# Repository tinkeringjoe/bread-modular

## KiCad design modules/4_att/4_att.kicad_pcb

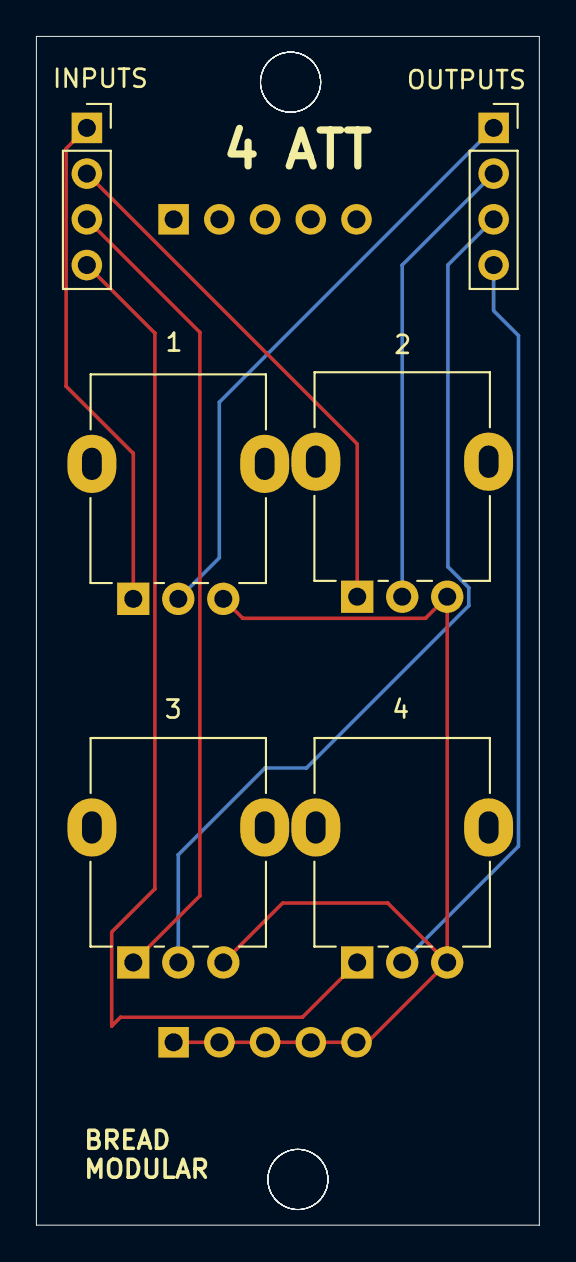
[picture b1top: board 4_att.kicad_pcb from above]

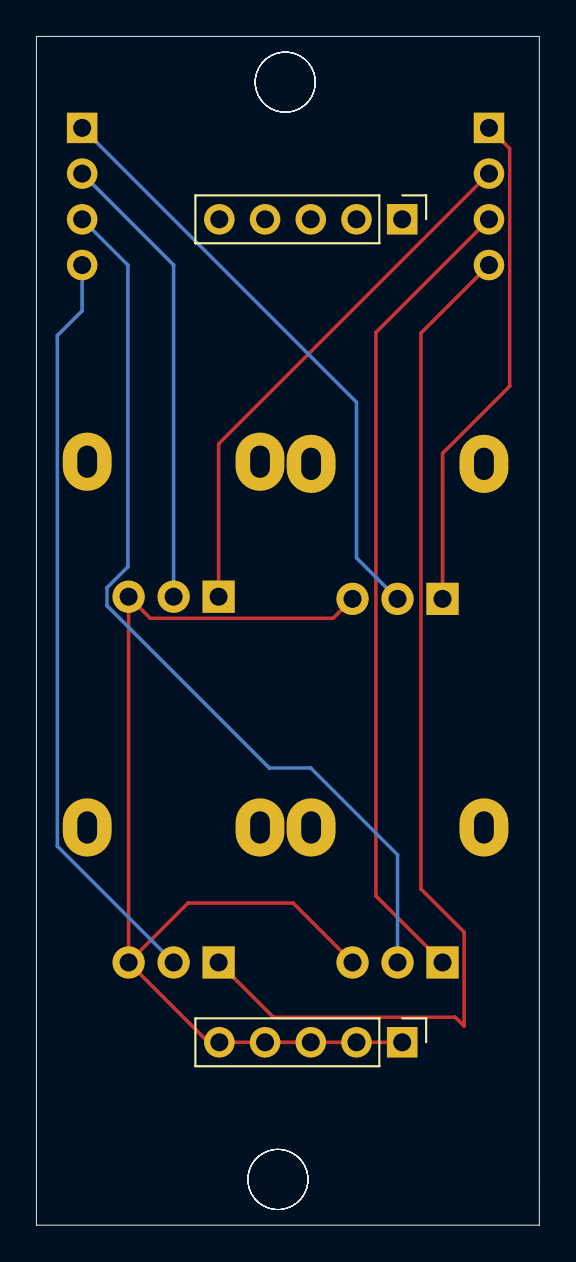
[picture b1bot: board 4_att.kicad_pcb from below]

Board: 2 copper layers, 27.9 x 66.0 mm, 8 parts (2 on the bottom side), 9 nets.

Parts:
1, 2, 3, 4: 100K; Potentiometer_Alpha_RD901F-40-00D_Single_Vertical
5V1: Conn_01x05_Pin; PinHeader_1x05_P2.54mm_Vertical
GND1: Conn_01x05_Pin; PinHeader_1x05_P2.54mm_Vertical
INPUTS: Conn_01x04_Socket; PinSocket_1x04_P2.54mm_Vertical
OUTPUTS: Conn_01x04_Socket; PinSocket_1x04_P2.54mm_Vertical

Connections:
GND: 1.3, 2.3, 3.3, 4.3, GND1.1, GND1.2, GND1.3, GND1.4, GND1.5
IN 1: 1.1, INPUTS.1
IN 2: 2.1, INPUTS.2
IN 3: 3.1, INPUTS.3
IN 4: 4.1, INPUTS.4
OUT 1: 1.2, OUTPUTS.1
OUT 2: 2.2, OUTPUTS.2
OUT 3: 3.2, OUTPUTS.3
OUT 4: 4.2, OUTPUTS.4

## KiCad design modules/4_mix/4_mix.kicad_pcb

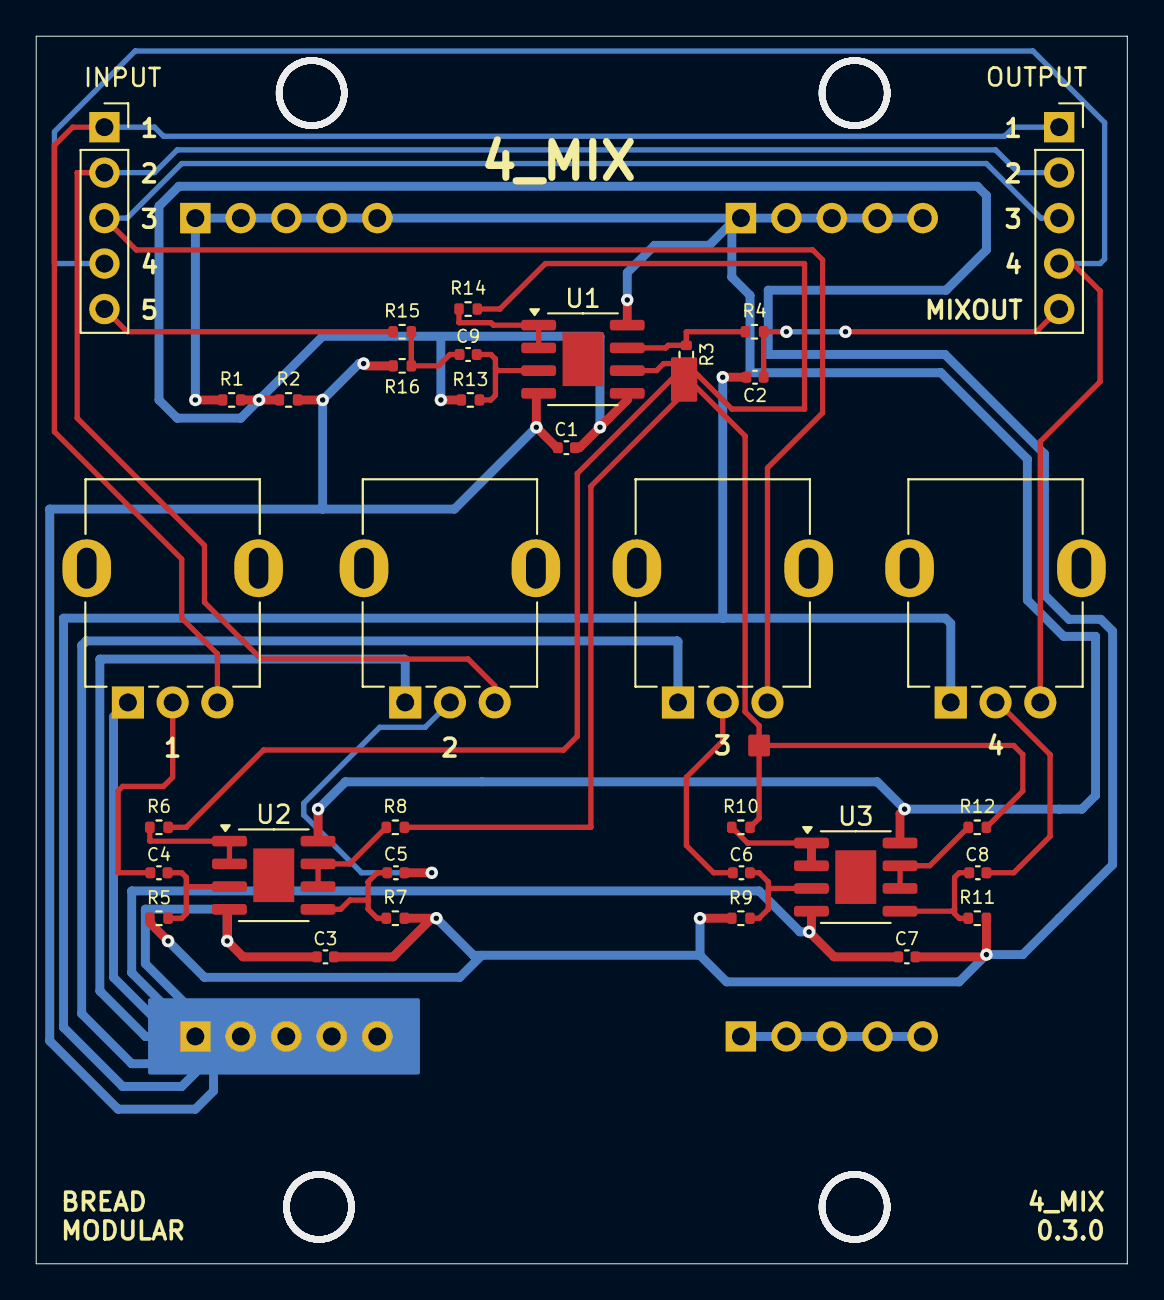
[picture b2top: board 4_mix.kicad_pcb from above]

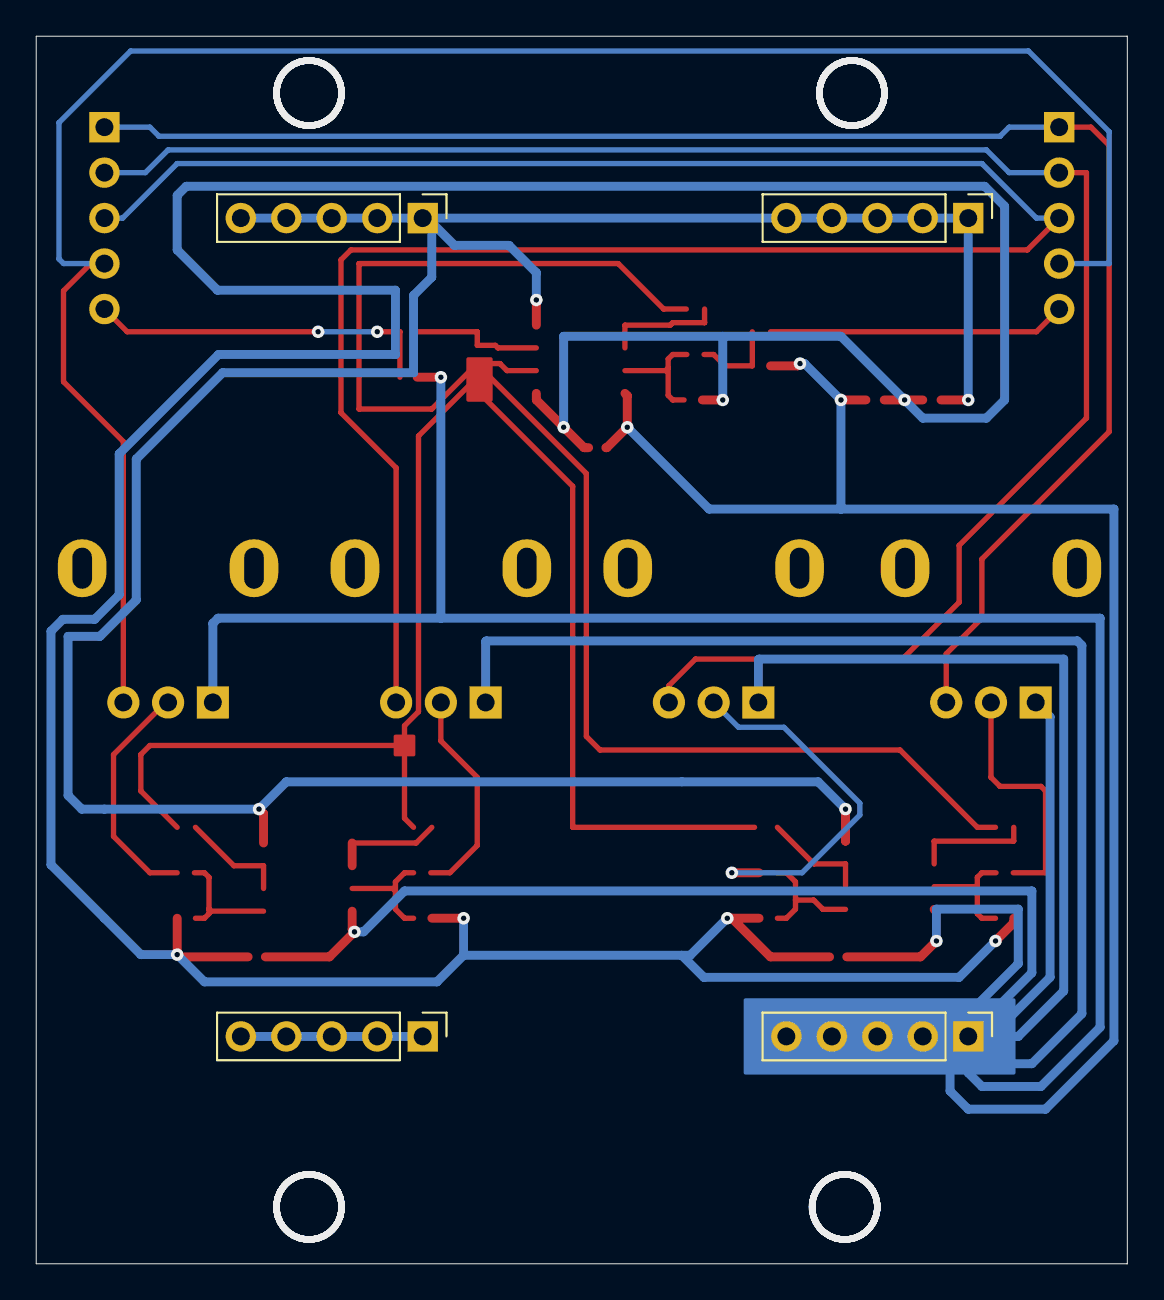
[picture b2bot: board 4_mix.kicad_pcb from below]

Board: 2 copper layers, 61.0 x 68.6 mm, 38 parts (4 on the bottom side), 27 nets.

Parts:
1, 2, 3, 4: 50k; Potentiometer_RV09
5V1, 5V2: Conn_01x05_Pin; PinHeader_1x05_P2.54mm_Vertical
C1, C3, C4, C5, C6, C7, C8, C9: 0.1uf; C_0402_1005Metric
C2: 0.01uf; C_0402_1005Metric
GND1, GND2: Conn_01x05_Pin; PinHeader_1x05_P2.54mm_Vertical
INPUT: Conn_01x05_Socket; PinSocket_1x05_P2.54mm_Vertical
OUTPUT: Conn_01x05_Socket; PinSocket_1x05_P2.54mm_Vertical
R1, R2, R4, R15: 1k; R_0402_1005Metric
R3, R5, R6, R7, R8, R9, R10, R11, R12, R13, R14: 100k; R_0402_1005Metric
R16: 51k; R_0402_1005Metric
U1, U2, U3: TL072; SOIC-8-1EP_3.9x4.9mm_P1.27mm_EP2.29x3mm

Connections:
2.5V: C1.2, C3.2, C7.2, R1.2, R2.1, R5.2, R7.2, R9.2, R11.2, R13.2, U1.5 (+)
+5V: 5V1.1, 5V1.2, 5V1.3, 5V1.4, 5V1.5, 5V2.1, 5V2.2, 5V2.3, 5V2.4, 5V2.5, R1.1, U1.8 (V+), U2.8 (V+), U3.8 (V+)
GND: 1.1, 2.1, 3.1, 4.1, C1.1, C2.2, C3.1, C7.1, GND1.1, GND1.2, GND1.3, GND1.4, GND1.5, R2.2, R16.2, U1.4 (V-), U2.4 (V-), U3.4 (V-)
IN_1: 1.3, INPUT.1, OUTPUT.1
IN_2: 2.3, INPUT.2, OUTPUT.2
IN_3: 3.3, INPUT.3, OUTPUT.3
IN_4: 4.3, INPUT.4, OUTPUT.4
IN_5: INPUT.5, R15.1
MIXOUT: C2.1, OUTPUT.5, R4.2
unnamed: 1.2, C4.1
unnamed: 2.2, C5.1
unnamed: 3.2, C6.1
unnamed: 4.2, C8.1
unnamed: C9.1, R15.2, R16.1
unnamed: GND2.1, GND2.2, GND2.3, GND2.4, GND2.5
unnamed: R3.2, R4.1, U1.7
unnamed: C9.2, R13.1, U1.3 (+)
unnamed: R3.1, R6.2, R8.2, R10.2, R12.2, R14.2, U1.6 (-)
unnamed: C4.2, R5.1, U2.3 (+)
unnamed: R6.1, U2.1, U2.2 (-)
unnamed: C5.2, R7.1, U2.5 (+)
unnamed: R8.1, U2.6 (-), U2.7
unnamed: C6.2, R9.1, U3.3 (+)
unnamed: R10.1, U3.1, U3.2 (-)
unnamed: C8.2, R11.1, U3.5 (+)
unnamed: R12.1, U3.6 (-), U3.7
OUT_5: R14.1, U1.1, U1.2 (-)

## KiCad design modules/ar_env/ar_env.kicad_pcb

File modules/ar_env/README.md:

# AR ENV

A Simple Attack/Release Envelope.

This has three controls:

* Attack
* Release
* Shape - Controls the duty cycle. Only works when the "SIG" input is a triangle signal. 

> Make sure to keep the Shape at pos=0.5 when using the square wave inputs.

## Known Errors

* When the Attack & Release is close to zero, this module leaks some pops to the ground.
(So, it will pick up by the line-out)
* When the input is above 5Hz, it's very hard to control Attack & Release. (We need to wiggle between pos=0.0 & pos=0.2)
* Using with JVCA gives more controls, but it will be confusing sometimes. Especially JVCA has a built-in delay effect for changes.
(It could be a feature too)
A simple Vactral based VCA would fix it. (V2CA)

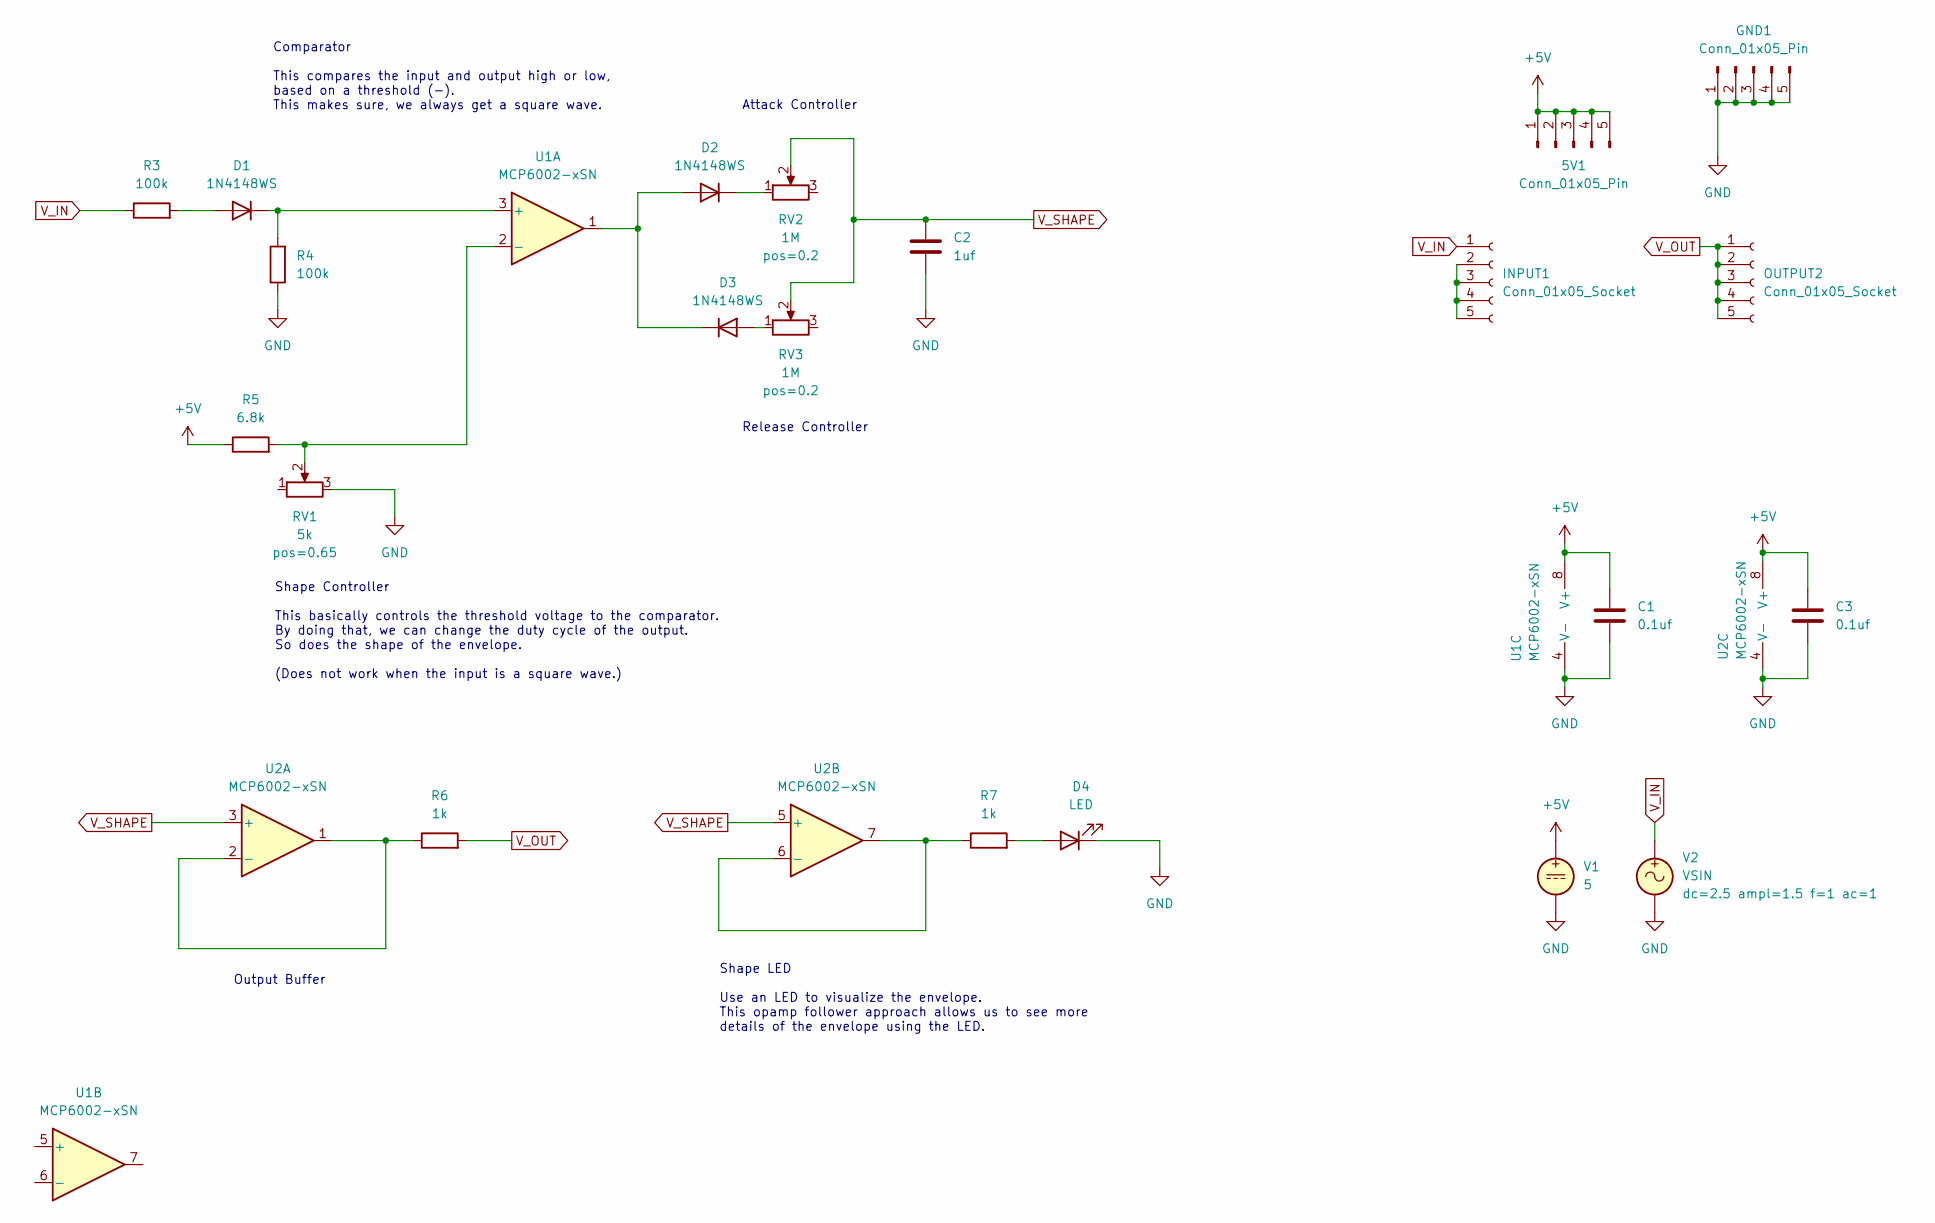
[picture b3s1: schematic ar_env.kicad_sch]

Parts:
5V1: Conn_01x05_Pin; PinHeader_1x05_P2.54mm_Vertical
C1, C3: 0.1uf; C_0402_1005Metric
C2: 1uf; C_1206_3216Metric
D1, D2, D3: 1N4148WS; D_SOD-323_HandSoldering
D4: LED; LED_0603_1608Metric
GND1: Conn_01x05_Pin; PinHeader_1x05_P2.54mm_Vertical
INPUT1: Conn_01x05_Socket; PinSocket_1x05_P2.54mm_Vertical
OUTPUT2: Conn_01x05_Socket; PinSocket_1x05_P2.54mm_Vertical
R3, R4: 100k; R_0402_1005Metric
R5: 6.8k; R_0603_1608Metric
R6, R7: 1k; R_0402_1005Metric
RV1: 5k; Potentiometer_RV09
RV2, RV3: 1M; Potentiometer_RV09
U1, U2: MCP6002-xSN; SOIC-8-1EP_3.9x4.9mm_P1.27mm_EP2.29x3mm
V1: 5
V2: VSIN

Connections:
+5V: 5V1.1, 5V1.2, 5V1.3, 5V1.4, 5V1.5, C1.1, C3.1, R5.1, U1.8 (V+), U2.8 (V+), V1.1
GND: C1.2, C2.2, C3.2, D4.1 (K), GND1.1, GND1.2, GND1.3, GND1.4, GND1.5, R4.1, RV1.3, U1.4 (V-), U2.4 (V-), V1.2, V2.2
unnamed: D1.2 (A), R3.2
unnamed: D1.1 (K), R4.2, U1.3 (+)
unnamed: D2.2 (A), D3.1 (K), U1.1
unnamed: D2.1 (K), RV2.1
unnamed: D3.2 (A), RV3.1
unnamed: D4.2 (A), R7.2
unnamed: INPUT1.2, INPUT1.3, INPUT1.4, INPUT1.5
unnamed: R5.2, RV1.2, U1.2 (-)
unnamed: R6.1, U2.1, U2.2 (-)
unnamed: R7.1, U2.6 (-), U2.7
V_IN: INPUT1.1, R3.1, V2.1
V_OUT: OUTPUT2.1, OUTPUT2.2, OUTPUT2.3, OUTPUT2.4, OUTPUT2.5, R6.2
V_SHAPE: C2.1, RV2.2, RV3.2, U2.3 (+), U2.5 (+)

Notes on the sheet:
Shape LED Use an LED to visualize the envelope. This opamp follower approach allows us to see more details of the envelope using the LED.
Shape Controller This basically controls the threshold voltage to the comparator. By doing that, we can change the duty cycle of the output. So does the shape of the envelope. (Does not work when the input is a square wave.)
Release Controller
Output Buffer
Attack Controller
Comparator This compares the input and output high or low, based on a threshold (-). This makes sure, we always get a square wave.

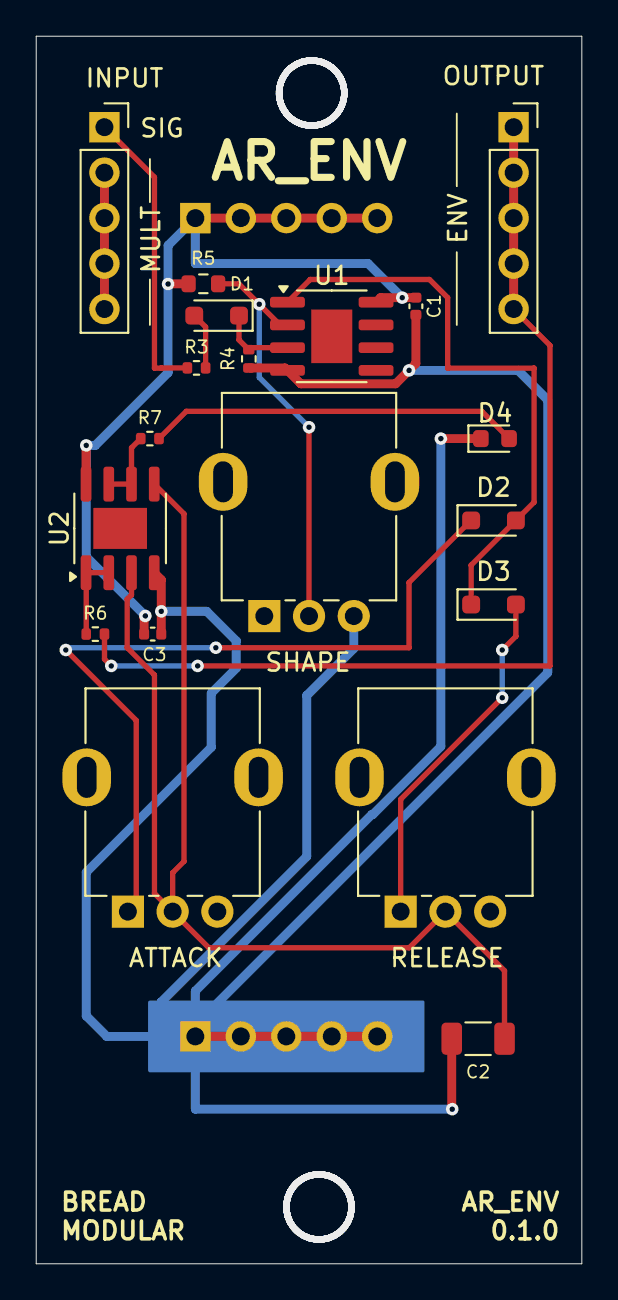
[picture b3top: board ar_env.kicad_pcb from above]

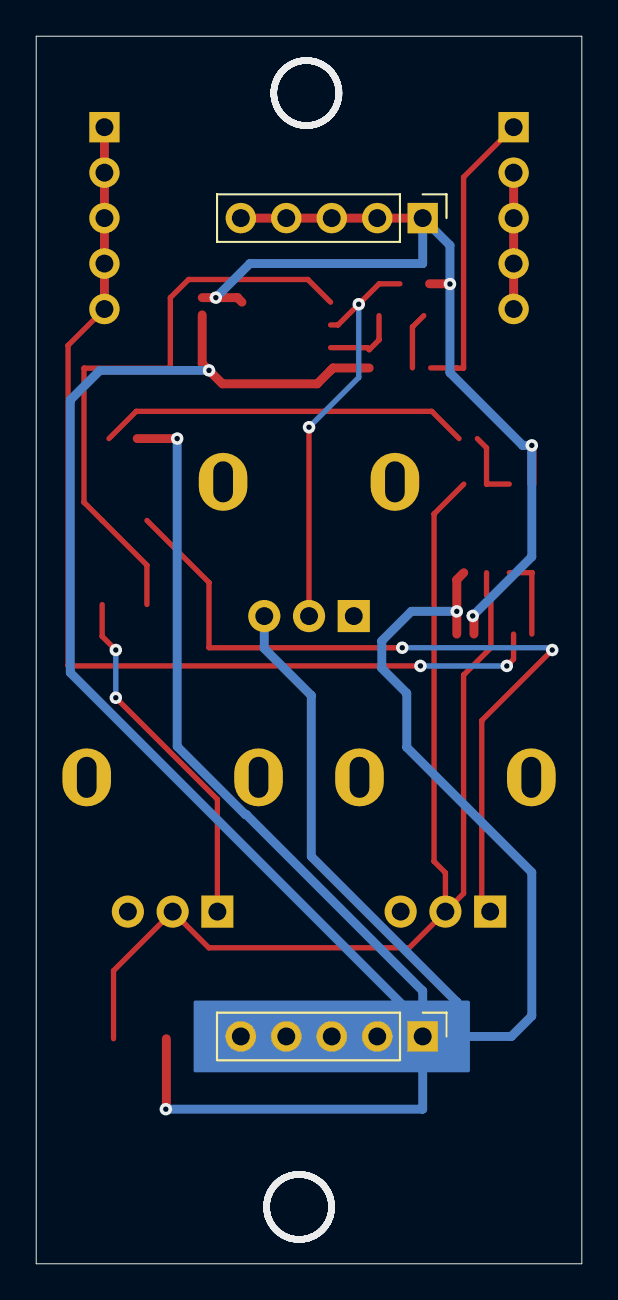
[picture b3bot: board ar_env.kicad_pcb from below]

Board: 2 copper layers, 30.5 x 68.6 mm, 21 parts (2 on the bottom side), 15 nets.

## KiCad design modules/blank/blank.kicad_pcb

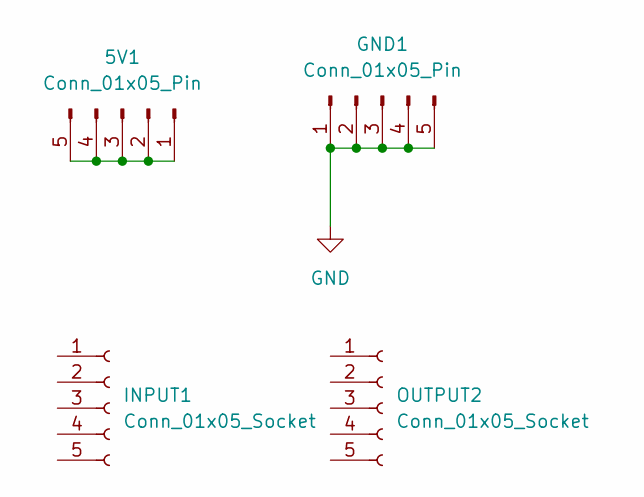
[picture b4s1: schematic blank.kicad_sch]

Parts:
5V1: Conn_01x05_Pin; PinHeader_1x05_P2.54mm_Vertical
GND1: Conn_01x05_Pin; PinHeader_1x05_P2.54mm_Vertical
INPUT1: Conn_01x05_Socket; PinSocket_1x05_P2.54mm_Vertical
OUTPUT2: Conn_01x05_Socket; PinSocket_1x05_P2.54mm_Vertical

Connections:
+5V: 5V1.1, 5V1.2, 5V1.3, 5V1.4, 5V1.5
GND: GND1.1, GND1.2, GND1.3, GND1.4, GND1.5

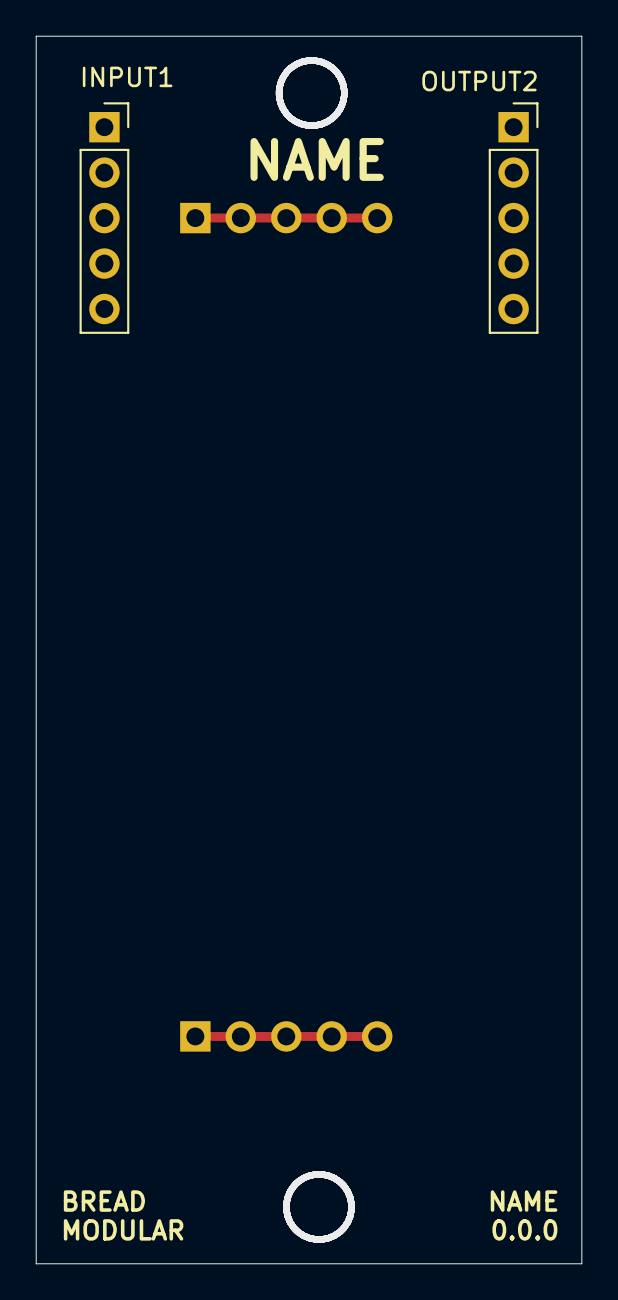
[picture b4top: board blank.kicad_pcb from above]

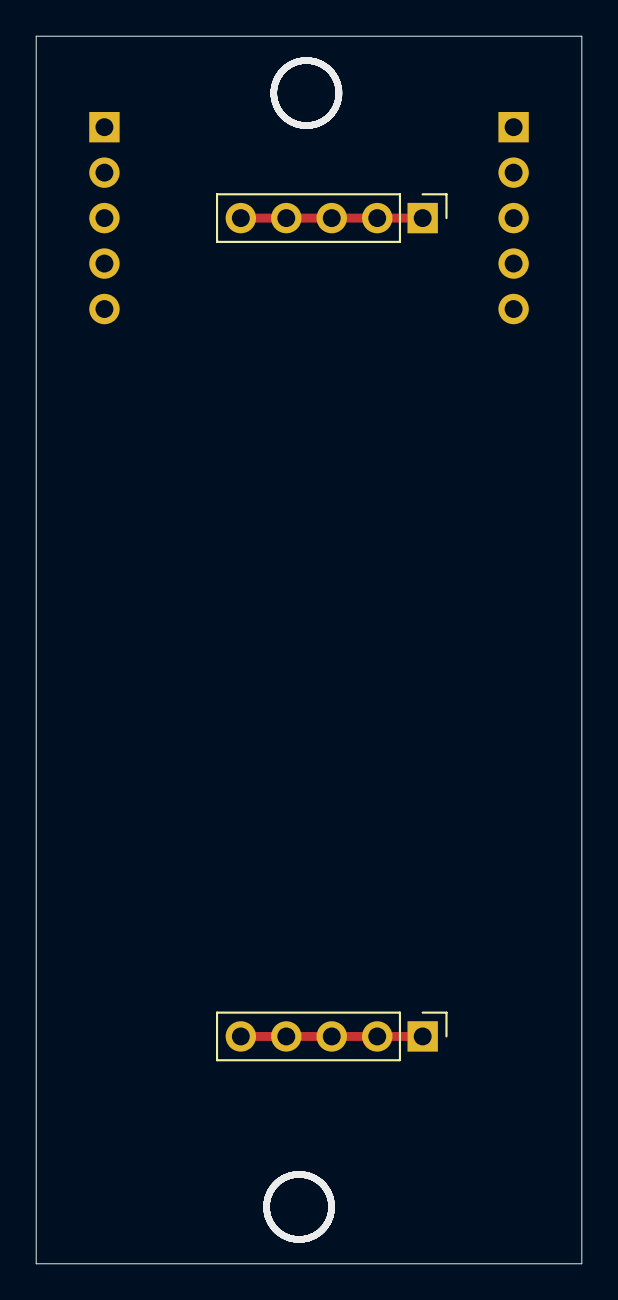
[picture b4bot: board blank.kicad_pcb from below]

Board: 2 copper layers, 30.5 x 68.6 mm, 4 parts (2 on the bottom side), 2 nets.

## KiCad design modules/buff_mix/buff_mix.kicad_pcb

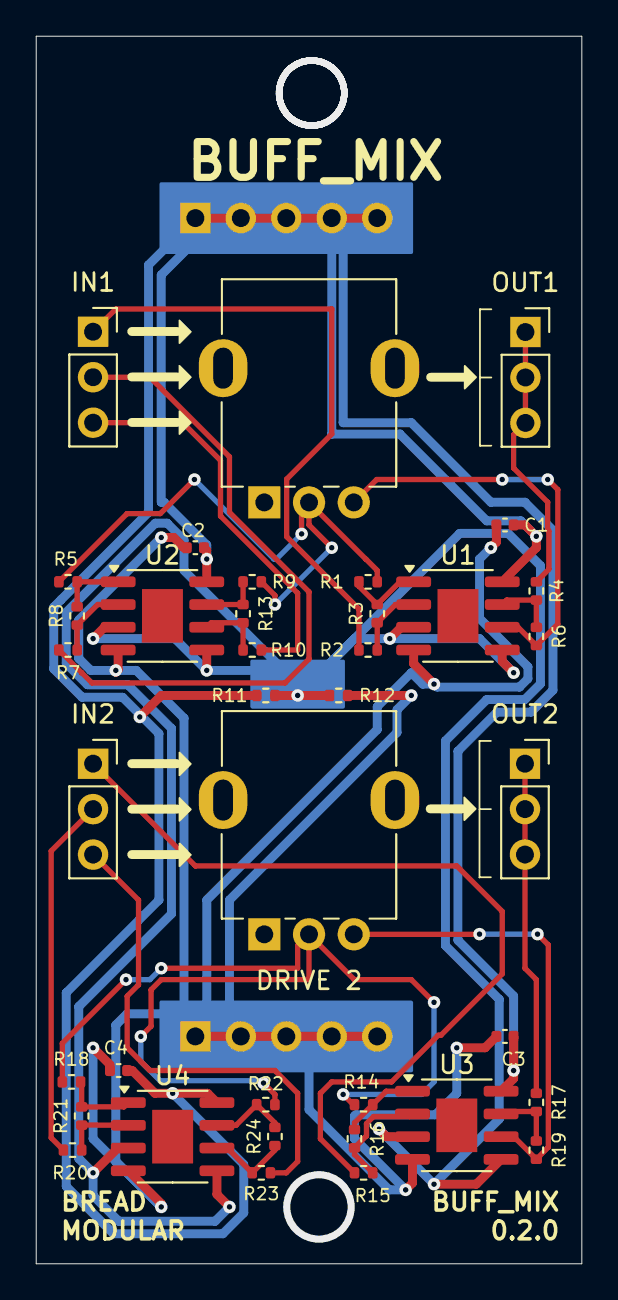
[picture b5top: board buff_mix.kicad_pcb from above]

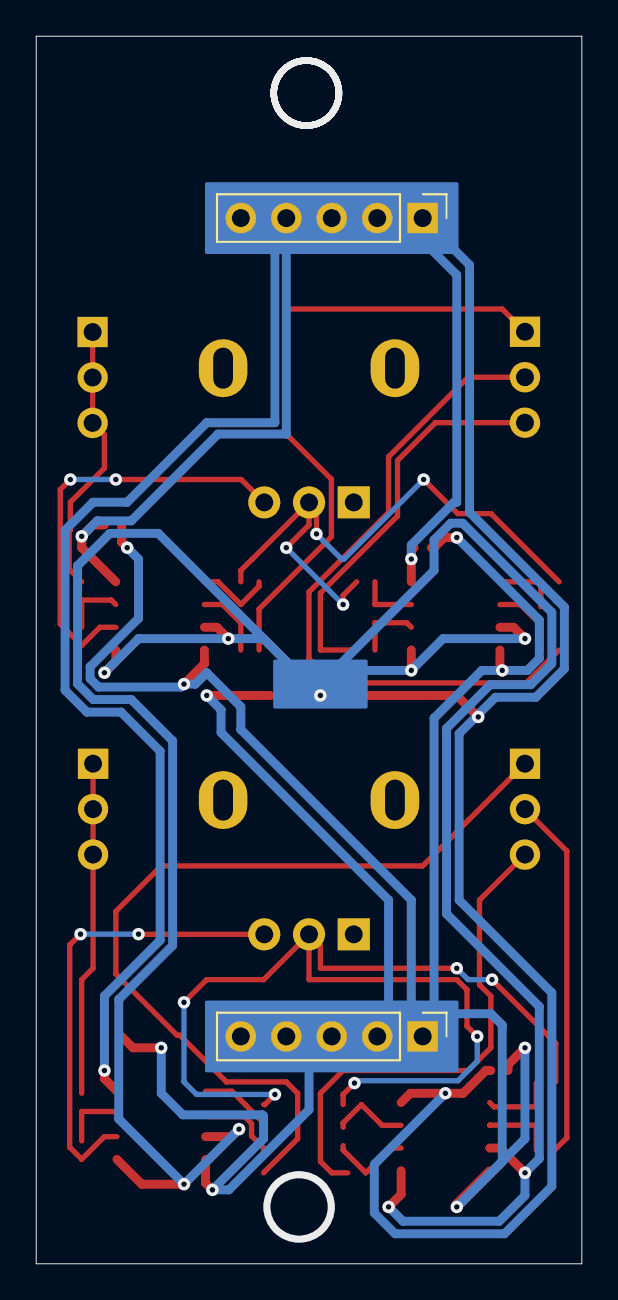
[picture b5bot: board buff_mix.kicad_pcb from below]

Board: 2 copper layers, 30.5 x 68.6 mm, 40 parts (2 on the bottom side), 29 nets.

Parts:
5V1: Conn_01x05_Pin; PinHeader_1x05_P2.54mm_Vertical
C1, C2, C3, C4: 0.1uf; C_0402_1005Metric
GND1: Conn_01x05_Pin; PinHeader_1x05_P2.54mm_Vertical
IN1, IN2: Conn_01x03_Socket; PinSocket_1x03_P2.54mm_Vertical
OUT1, OUT2: Conn_01x03_Socket; PinSocket_1x03_P2.54mm_Vertical
R1, R2, R3, R5, R6, R7, R8, R9, R10, R13, R14, R15, R16, R18, R19, R20, R21, R22, R23, R24: 1M; R_0402_1005Metric
R4, R11, R12, R17: 1k; R_0402_1005Metric
RV1, RV2: 1M; Potentiometer_RV09
U1, U2, U3, U4: MCP6002-xSN; SOIC-8-1EP_3.9x4.9mm_P1.27mm_EP2.29x3mm

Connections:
+2.5V: R11.2, R12.1, U1.3 (+), U1.5 (+), U2.3 (+), U2.5 (+), U3.3 (+), U3.5 (+), U4.3 (+), U4.5 (+)
+5V: 5V1.1, 5V1.2, 5V1.3, 5V1.4, 5V1.5, C1.1, C2.1, C3.1, C4.1, R11.1, U1.8 (V+), U2.8 (V+), U3.8 (V+), U4.8 (V+)
GND: C1.2, C2.2, C3.2, C4.2, GND1.1, GND1.2, GND1.3, GND1.4, GND1.5, R12.2, U1.4 (V-), U2.4 (V-), U3.4 (V-), U4.4 (V-)
INA_1: IN1.1, R2.1
INA_2: IN1.2, R7.1
INA_3: IN1.3, R10.1
INB_1: IN2.1, R15.1
INB_2: IN2.2, R20.1
INB_3: IN2.3, R23.1
unnamed: R1.1, R3.2, U1.1
unnamed: R1.2, R5.2, R9.2, RV1.2
unnamed: R4.1, R6.2, U1.7
unnamed: R5.1, R8.2, U2.1
unnamed: R9.1, R13.2, U2.7
unnamed: R14.1, R16.2, U3.1
unnamed: R14.2, R18.2, R22.2, RV2.2
unnamed: R17.1, R19.2, U3.7
unnamed: R18.1, R21.2, U4.1
unnamed: R22.1, R24.2, U4.7
unnamed: R2.2, R3.1, U1.2 (-)
unnamed: R6.1, RV1.3, U1.6 (-)
unnamed: R7.2, R8.1, U2.2 (-)
unnamed: R10.2, R13.1, U2.6 (-)
unnamed: R15.2, R16.1, U3.2 (-)
unnamed: R19.1, RV2.3, U3.6 (-)
unnamed: R20.2, R21.1, U4.2 (-)
unnamed: R23.2, R24.1, U4.6 (-)
OUTA: OUT1.1, OUT1.2, OUT1.3, R4.2
OUTB: OUT2.1, OUT2.2, OUT2.3, R17.2

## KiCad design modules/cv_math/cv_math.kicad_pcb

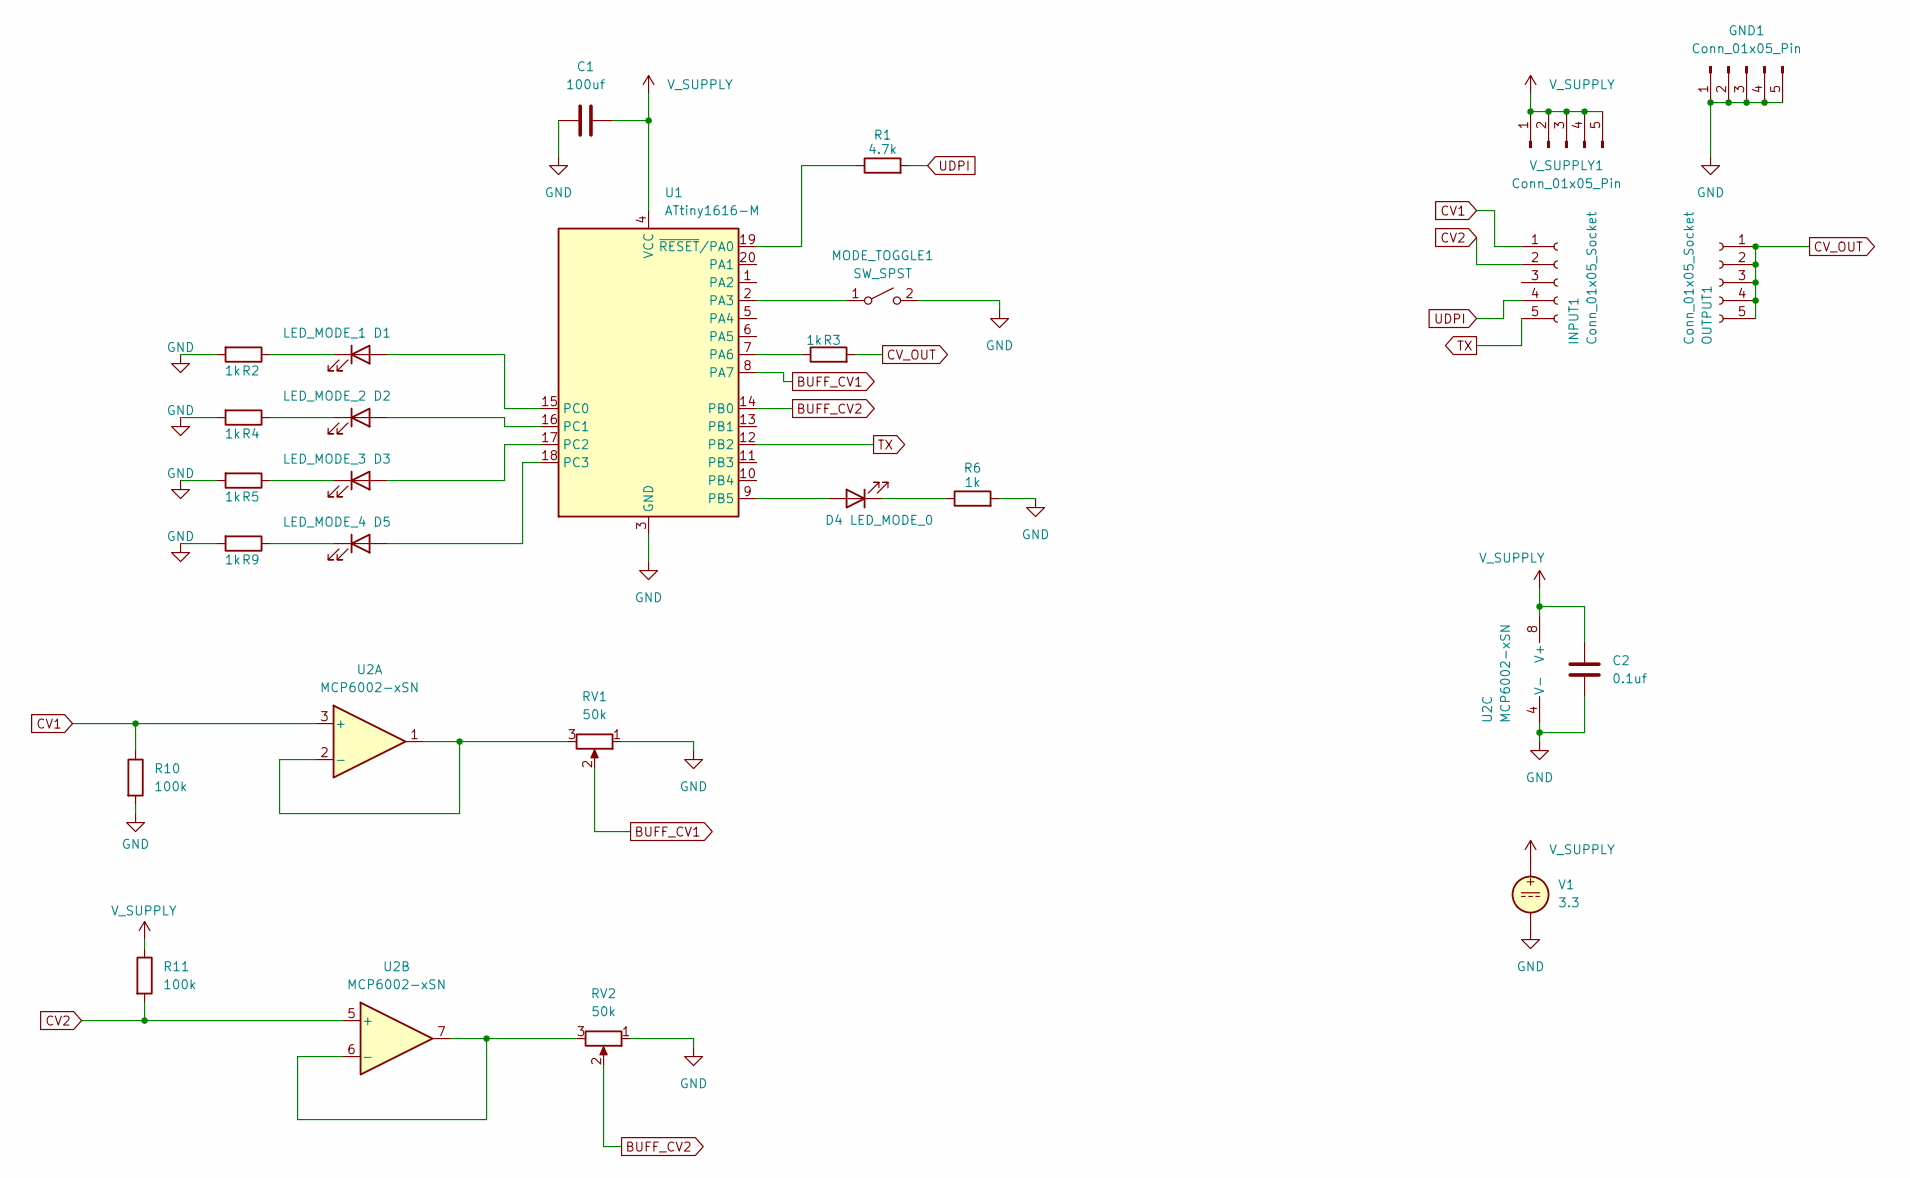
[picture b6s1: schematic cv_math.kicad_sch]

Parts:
C1: 100uf; C_1206_3216Metric
C2: 0.1uf; C_0402_1005Metric
D1: LED_MODE_1; LED_0603_1608Metric
D2: LED_MODE_2; LED_0603_1608Metric
D3: LED_MODE_3; LED_0603_1608Metric
D4: LED_MODE_0; LED_0603_1608Metric
D5: LED_MODE_4; LED_0603_1608Metric
GND1: Conn_01x05_Pin; Power_Connector
INPUT1: Conn_01x05_Socket; PinSocket_1x05_P2.54mm_Vertical
MODE_TOGGLE1: SW_SPST; SPST_TS-1187A-B-A-B
OUTPUT1: Conn_01x05_Socket; PinSocket_1x05_P2.54mm_Vertical
R1: 4.7k; R_0402_1005Metric
R2, R3, R4, R5, R6, R9: 1k; R_0402_1005Metric
R10, R11: 100k; R_0402_1005Metric
RV1, RV2: 50k; Potentiometer_RV09
U1: ATtiny1616-M; VQFN-20-1EP_3x3mm_P0.4mm_EP1.7x1.7mm
U2: MCP6002-xSN; SOIC-8-1EP_3.9x4.9mm_P1.27mm_EP2.29x3mm
V1: 3.3
V_SUPPLY1: Conn_01x05_Pin; Power_Connector

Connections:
BUFF_CV1: RV1.2, U1.8 (PA7)
BUFF_CV2: RV2.2, U1.14 (PB0)
CV1: INPUT1.1, R10.1, U2.3 (+)
CV2: INPUT1.2, R11.2, U2.5 (+)
CV_OUT: OUTPUT1.1, OUTPUT1.2, OUTPUT1.3, OUTPUT1.4, OUTPUT1.5, R3.2
GND: C1.1, C2.2, GND1.1, GND1.2, GND1.3, GND1.4, GND1.5, MODE_TOGGLE1.2 (B), R2.2, R4.2, R5.2, R6.2, R9.2, R10.2, RV1.1, RV2.1, U1.3 (GND), U1.21 (GND), U2.4 (V-), V1.2
unnamed: D1.2 (A), U1.15 (PC0)
unnamed: D1.1 (K), R2.1
unnamed: D2.2 (A), U1.16 (PC1)
unnamed: D2.1 (K), R4.1
unnamed: D3.2 (A), U1.17 (PC2)
unnamed: D3.1 (K), R5.1
unnamed: D4.2 (A), U1.9 (PB5)
unnamed: D4.1 (K), R6.1
unnamed: D5.2 (A), U1.18 (PC3)
unnamed: D5.1 (K), R9.1
unnamed: MODE_TOGGLE1.1 (A), U1.2 (PA3)
unnamed: R3.1, U1.7 (PA6)
unnamed: R1.1, U1.19 (~RESET/PA0)
unnamed: RV1.3, U2.1, U2.2 (-)
unnamed: RV2.3, U2.6 (-), U2.7
TX: INPUT1.5, U1.12 (PB2)
UDPI: INPUT1.4, R1.2
V_SUPPLY: C1.2, C2.1, R11.1, U1.4 (VCC), U2.8 (V+), V1.1, V_SUPPLY1.1, V_SUPPLY1.2, V_SUPPLY1.3, V_SUPPLY1.4, V_SUPPLY1.5

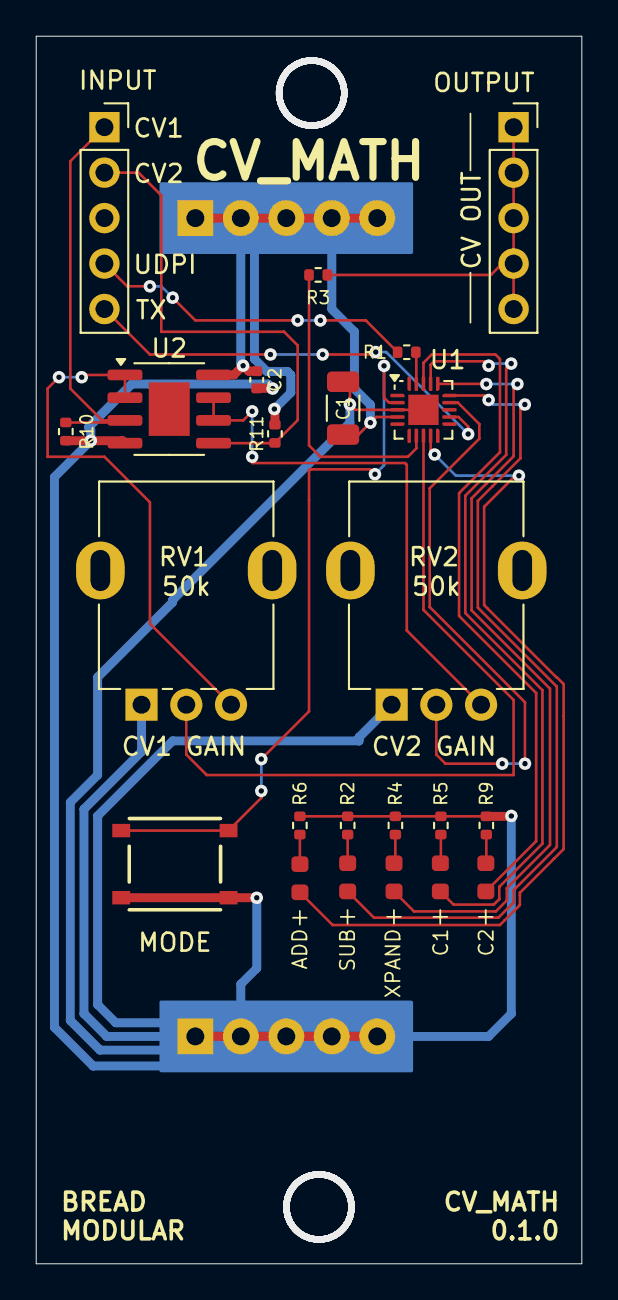
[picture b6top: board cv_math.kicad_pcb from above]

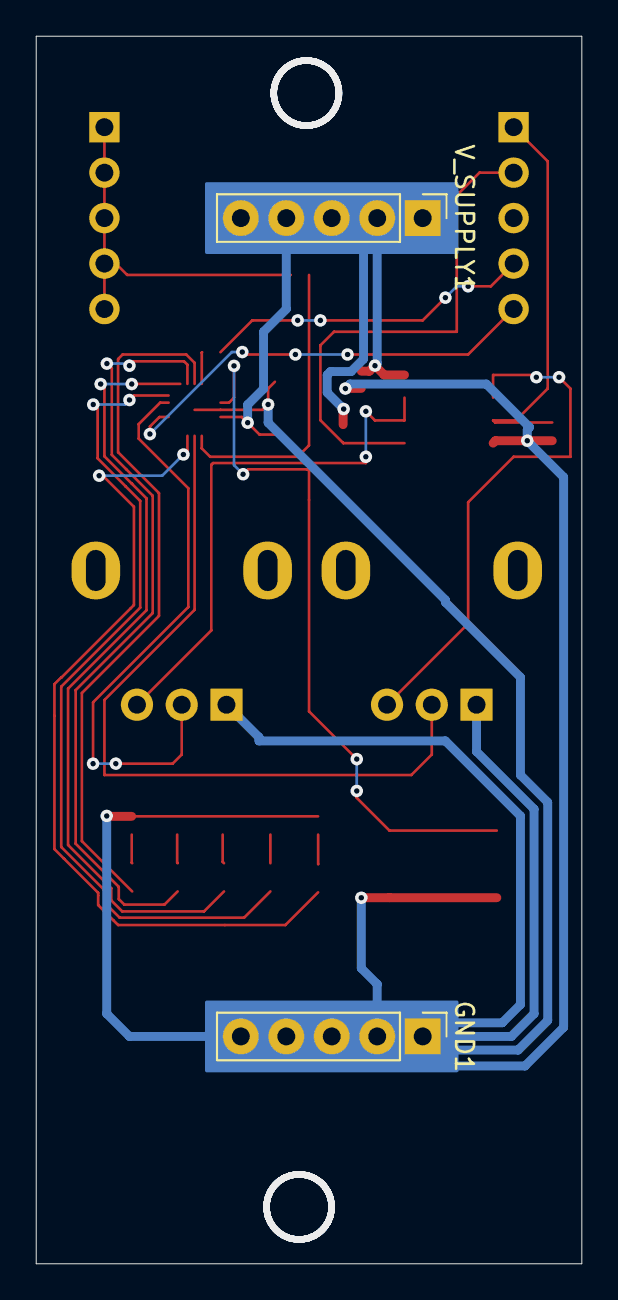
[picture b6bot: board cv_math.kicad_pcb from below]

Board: 2 copper layers, 30.5 x 68.6 mm, 25 parts (2 on the bottom side), 24 nets.
